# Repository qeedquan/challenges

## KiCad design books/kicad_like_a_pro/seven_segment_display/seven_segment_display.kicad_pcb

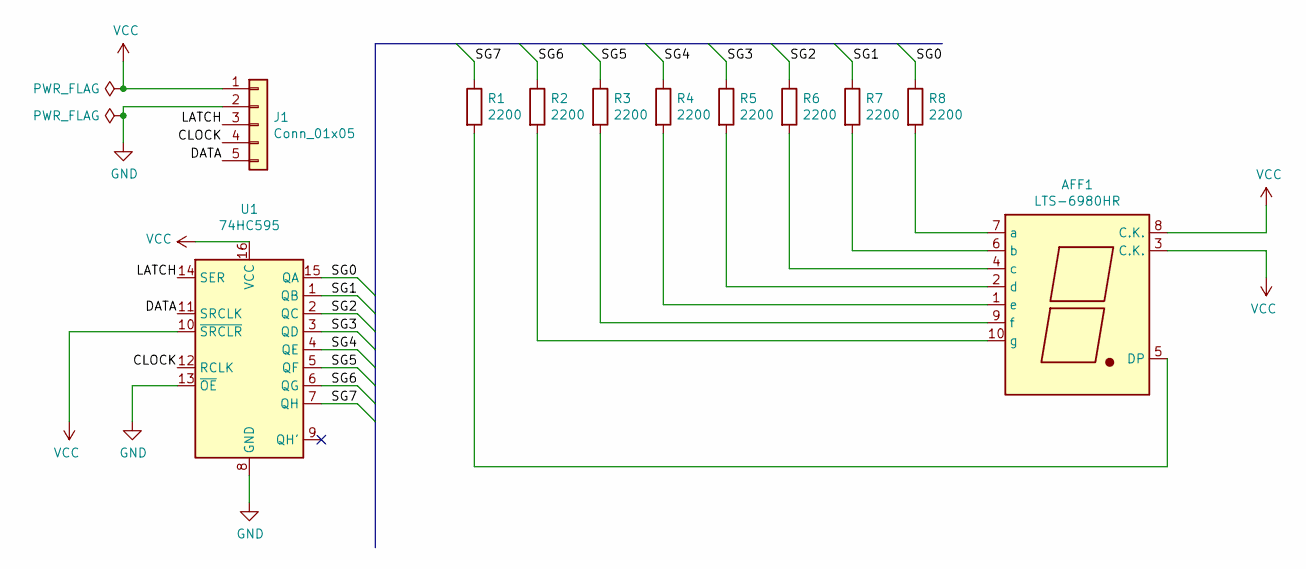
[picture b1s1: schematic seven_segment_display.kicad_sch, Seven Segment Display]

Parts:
AFF1: LTS-6980HR; 7SegmentLED_LTS6760_LTS6780
J1: Conn_01x05; PinHeader_1x05_P2.54mm_Horizontal
R1, R2, R3, R4, R5, R6, R7, R8: 2200; R_Axial_DIN0411_L9.9mm_D3.6mm_P25.40mm_Horizontal
U1: 74HC595; DIP16-2.54-20.32X5.84MM

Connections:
/CLOCK: J1.4, U1.12 (RCLK)
/DATA: J1.5, U1.11 (SRCLK)
/LATCH: J1.3, U1.14 (SER)
/SG0: R8.1, U1.15 (QA)
/SG1: R7.1, U1.1 (QB)
/SG2: R6.1, U1.2 (QC)
/SG3: R5.1, U1.3 (QD)
/SG4: R4.1, U1.4 (QE)
/SG5: R3.1, U1.5 (QF)
/SG6: R2.1, U1.6 (QG)
/SG7: R1.1, U1.7 (QH)
GND: J1.2, U1.8 (GND), U1.13 (~OE)
unnamed: AFF1.1 (e), R4.2
unnamed: AFF1.2 (d), R5.2
unnamed: AFF1.4 (c), R6.2
unnamed: AFF1.5 (DP), R1.2
unnamed: AFF1.6 (b), R7.2
unnamed: AFF1.7 (a), R8.2
unnamed: AFF1.9 (f), R3.2
unnamed: AFF1.10 (g), R2.2
VCC: AFF1.3 (C.K.), AFF1.8 (C.K.), J1.1, U1.10 (~SRCLR), U1.16 (VCC)

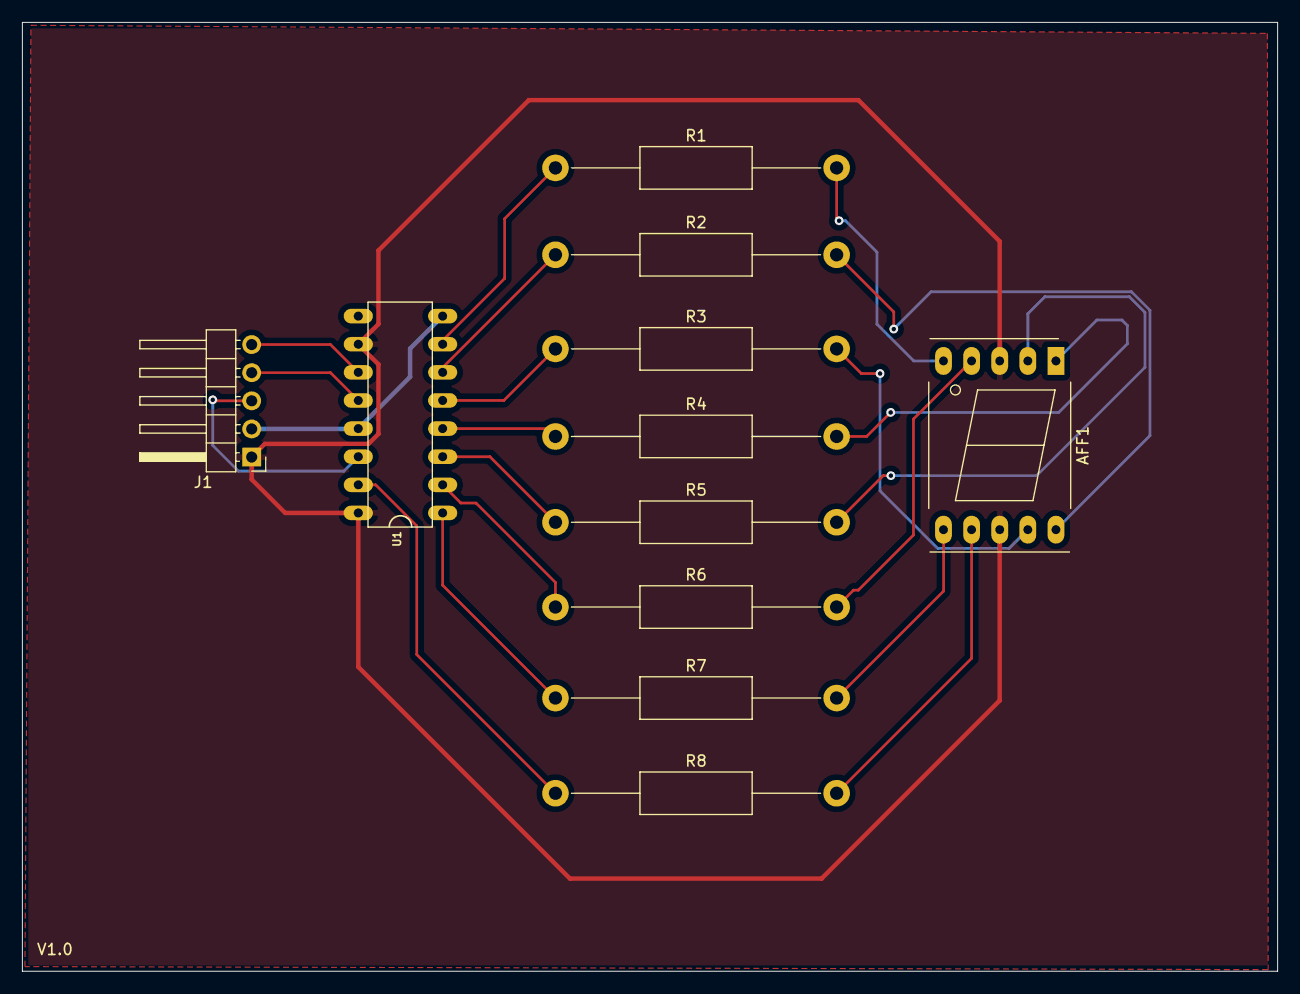
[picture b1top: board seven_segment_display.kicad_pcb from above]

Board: 2 copper layers, 113.4 x 85.7 mm, 11 parts (0 on the bottom side), 21 nets.

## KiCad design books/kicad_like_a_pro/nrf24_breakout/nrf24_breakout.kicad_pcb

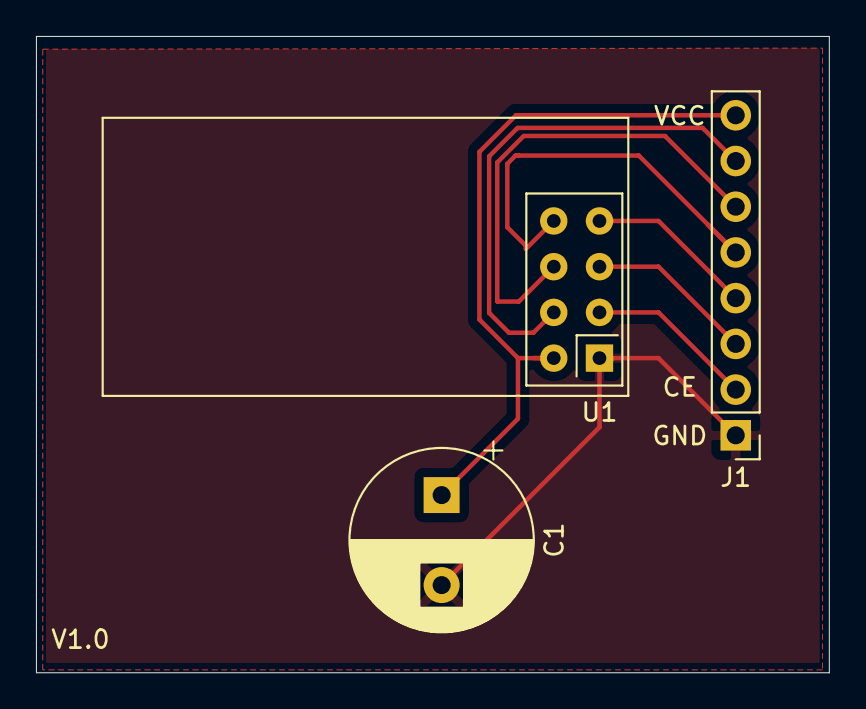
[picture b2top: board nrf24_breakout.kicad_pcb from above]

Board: 2 copper layers, 44.1 x 35.3 mm, 3 parts (0 on the bottom side), 8 nets.

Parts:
C1: CP1; CP_Radial_D10.0mm_P5.00mm
J1: Conn_01x08; PinHeader_1x08_P2.54mm_Vertical
U1: NRF24L01_Breakout; nRF24L01_Breakout

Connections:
GND: C1.2, J1.1, U1.1
unnamed: J1.2, U1.3
unnamed: J1.3, U1.5
unnamed: J1.4, U1.7
unnamed: J1.5, U1.8
unnamed: J1.6, U1.6
unnamed: J1.7, U1.4
VCC: C1.1, J1.8, U1.2

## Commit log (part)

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2021-07-13 initial
